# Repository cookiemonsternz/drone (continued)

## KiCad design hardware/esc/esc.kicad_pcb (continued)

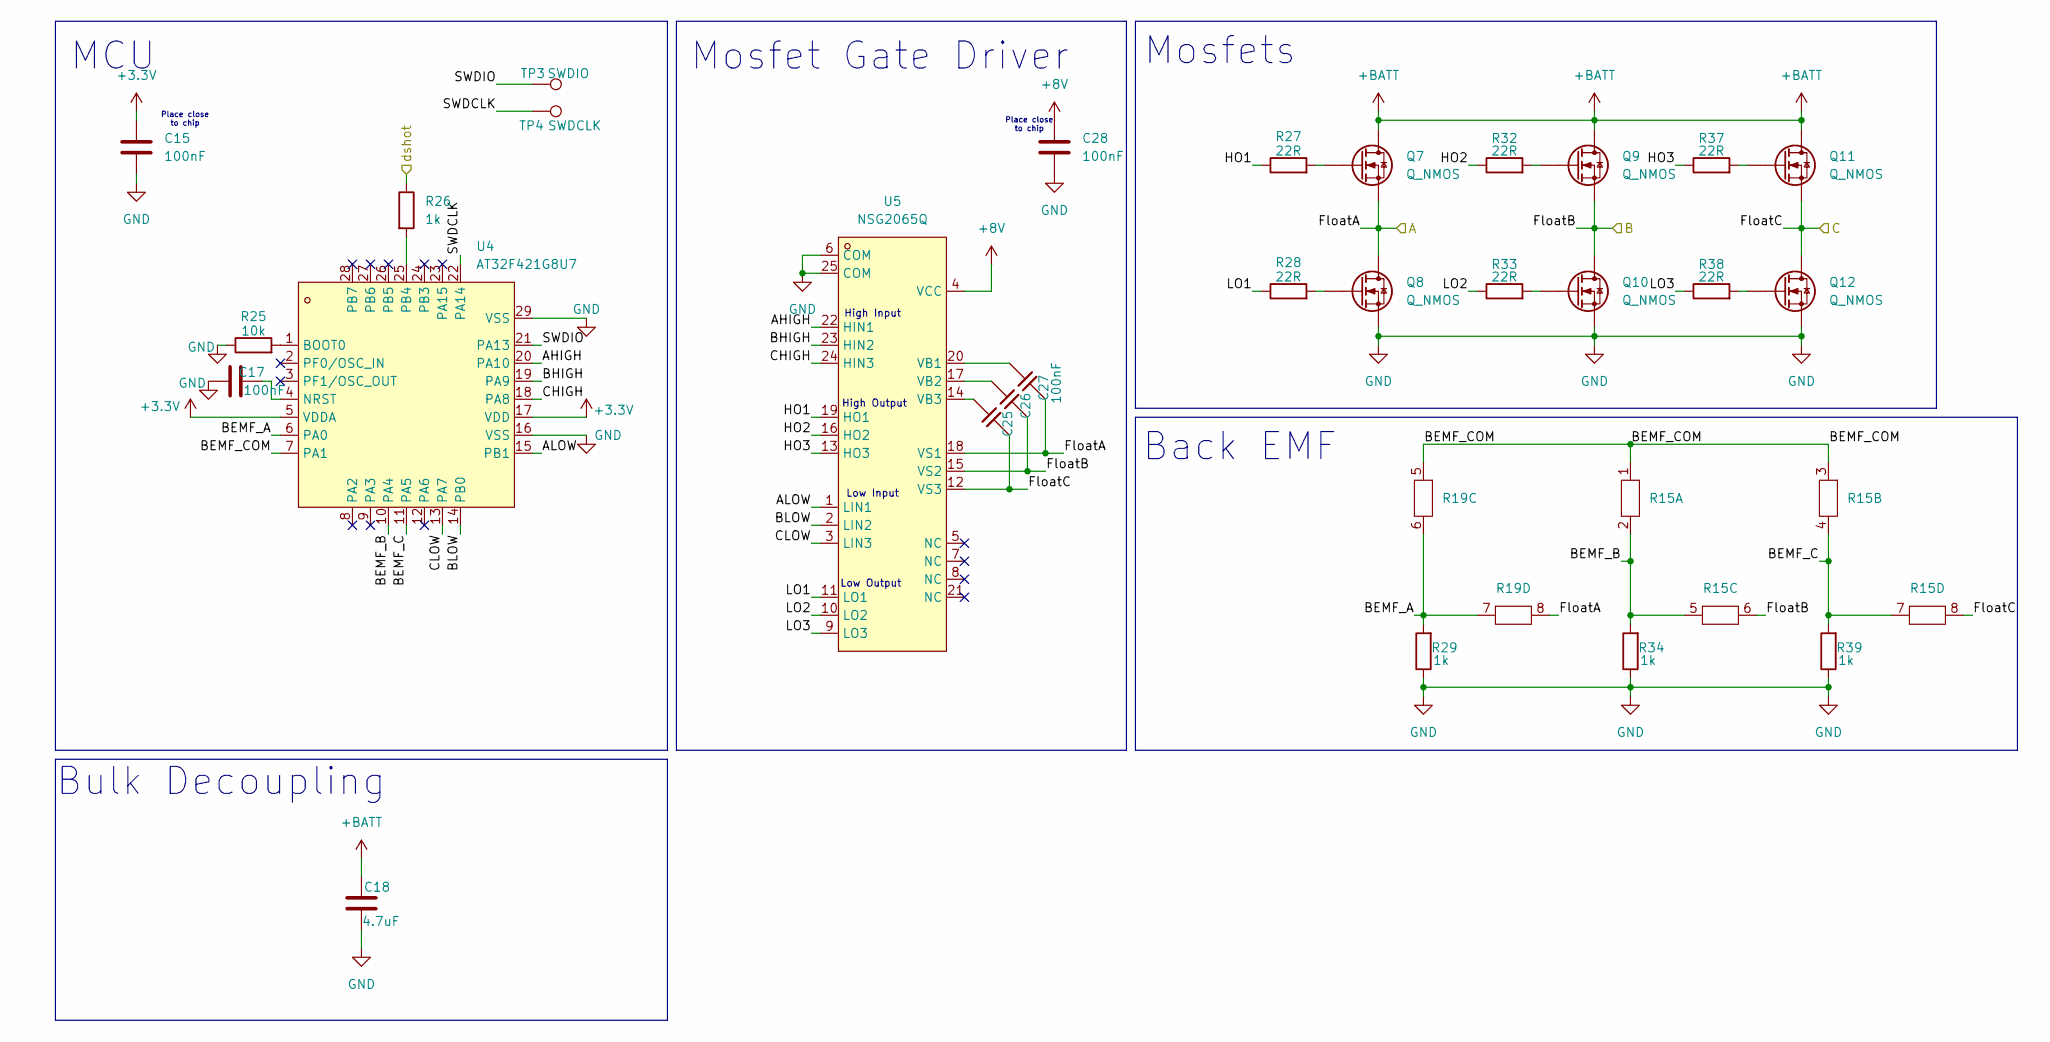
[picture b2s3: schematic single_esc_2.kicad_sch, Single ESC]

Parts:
C15, C17, C25, C26, C27, C28: 100nF; C_0402_1005Metric
C18: 4.7uF; C_0603_1608Metric
Q7, Q8, Q9, Q10, Q11, Q12: Q_NMOS; POWERPAK-1212-8_L3.0-W3.0-P0.65-LS3.3-BL
R15, R19: RES_4D03_0603_3P2X1P6_ROH
R25: 10k; R_0402_1005Metric
R26, R29, R34, R39: 1k; R_0402_1005Metric
R27, R28, R32, R33, R37, R38: 22R; R_0402_1005Metric
TP3: SWDIO; TestPoint_Pad_D1.0mm
TP4: SWDCLK; TestPoint_Pad_D1.0mm
U4: AT32F421G8U7; QFN-28_L4.0-W4.0-P0.40-TL-EP2.4; LCSC Part C2765098
U5: NSG2065Q; QFN-24_L4.0-W4.0-P0.50-TL-EP2.8; LCSC Part C41414478

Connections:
+3.3V: C15.1, U4.5 (VDDA), U4.17 (VDD); also elsewhere on the board
+8V: C28.1, U5.4 (VCC); also elsewhere on the board
+BATT: C18.1, Q7.D, Q9.D, Q11.D; also elsewhere on the board
/ESC2/AHIGH: U4.20 (PA10), U5.22 (HIN1)
/ESC2/ALOW: U4.15 (PB1), U5.1 (LIN1)
/ESC2/BEMF_A: R19.6, R19.7, R29.2, U4.6 (PA0)
/ESC2/BEMF_B: R15.2, R15.5, R34.2, U4.10 (PA4)
/ESC2/BEMF_C: R15.4, R15.7, R39.2, U4.11 (PA5)
/ESC2/BEMF_COM: R15.1, R15.3, R19.5, U4.7 (PA1)
/ESC2/BHIGH: U4.19 (PA9), U5.23 (HIN2)
/ESC2/BLOW: U4.14 (PB0), U5.2 (LIN2)
/ESC2/CHIGH: U4.18 (PA8), U5.24 (HIN3)
/ESC2/CLOW: U4.13 (PA7), U5.3 (LIN3)
/ESC2/FloatA: C27.1, Q7.S, Q8.D, R19.8, U5.18 (VS1); also elsewhere on the board
/ESC2/FloatB: C26.1, Q9.S, Q10.D, R15.6, U5.15 (VS2); also elsewhere on the board
/ESC2/FloatC: C25.1, Q11.S, Q12.D, R15.8, U5.12 (VS3); also elsewhere on the board
/ESC2/HO1: R27.1, U5.19 (HO1)
/ESC2/HO2: R32.1, U5.16 (HO2)
/ESC2/HO3: R37.1, U5.13 (HO3)
/ESC2/LO1: R28.1, U5.11 (LO1)
/ESC2/LO2: R33.1, U5.10 (LO2)
/ESC2/LO3: R38.1, U5.9 (LO3)
/ESC2/SWDCLK: TP4.1, U4.22 (PA14); also elsewhere on the board
/ESC2/SWDIO: TP3.1, U4.21 (PA13); also elsewhere on the board
/dshot_2: R26.1; also elsewhere on the board
GND: C15.2, C17.2, C18.2, C28.2, Q8.S, Q10.S, Q12.S, R25.1, R29.1, R34.1, R39.1, U4.16 (VSS), U4.29 (VSS), U5.6 (COM), U5.25 (COM); also elsewhere on the board
unnamed: Q7.G, R27.2
unnamed: Q8.G, R28.2
unnamed: Q9.G, R32.2
unnamed: Q10.G, R33.2
unnamed: Q11.G, R37.2
unnamed: Q12.G, R38.2
unnamed: R25.2, U4.1 (BOOT0)
unnamed: C17.1, U4.4 (NRST)
unnamed: R26.2, U4.25 (PB4)
unnamed: C27.2, U5.20 (VB1)
unnamed: C26.2, U5.17 (VB2)
unnamed: C25.2, U5.14 (VB3)

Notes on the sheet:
MCU
High Output
Back EMF
High Input
Mosfet Gate Driver
Mosfets
Bulk Decoupling
Low Output
Place close to chip
Low Input

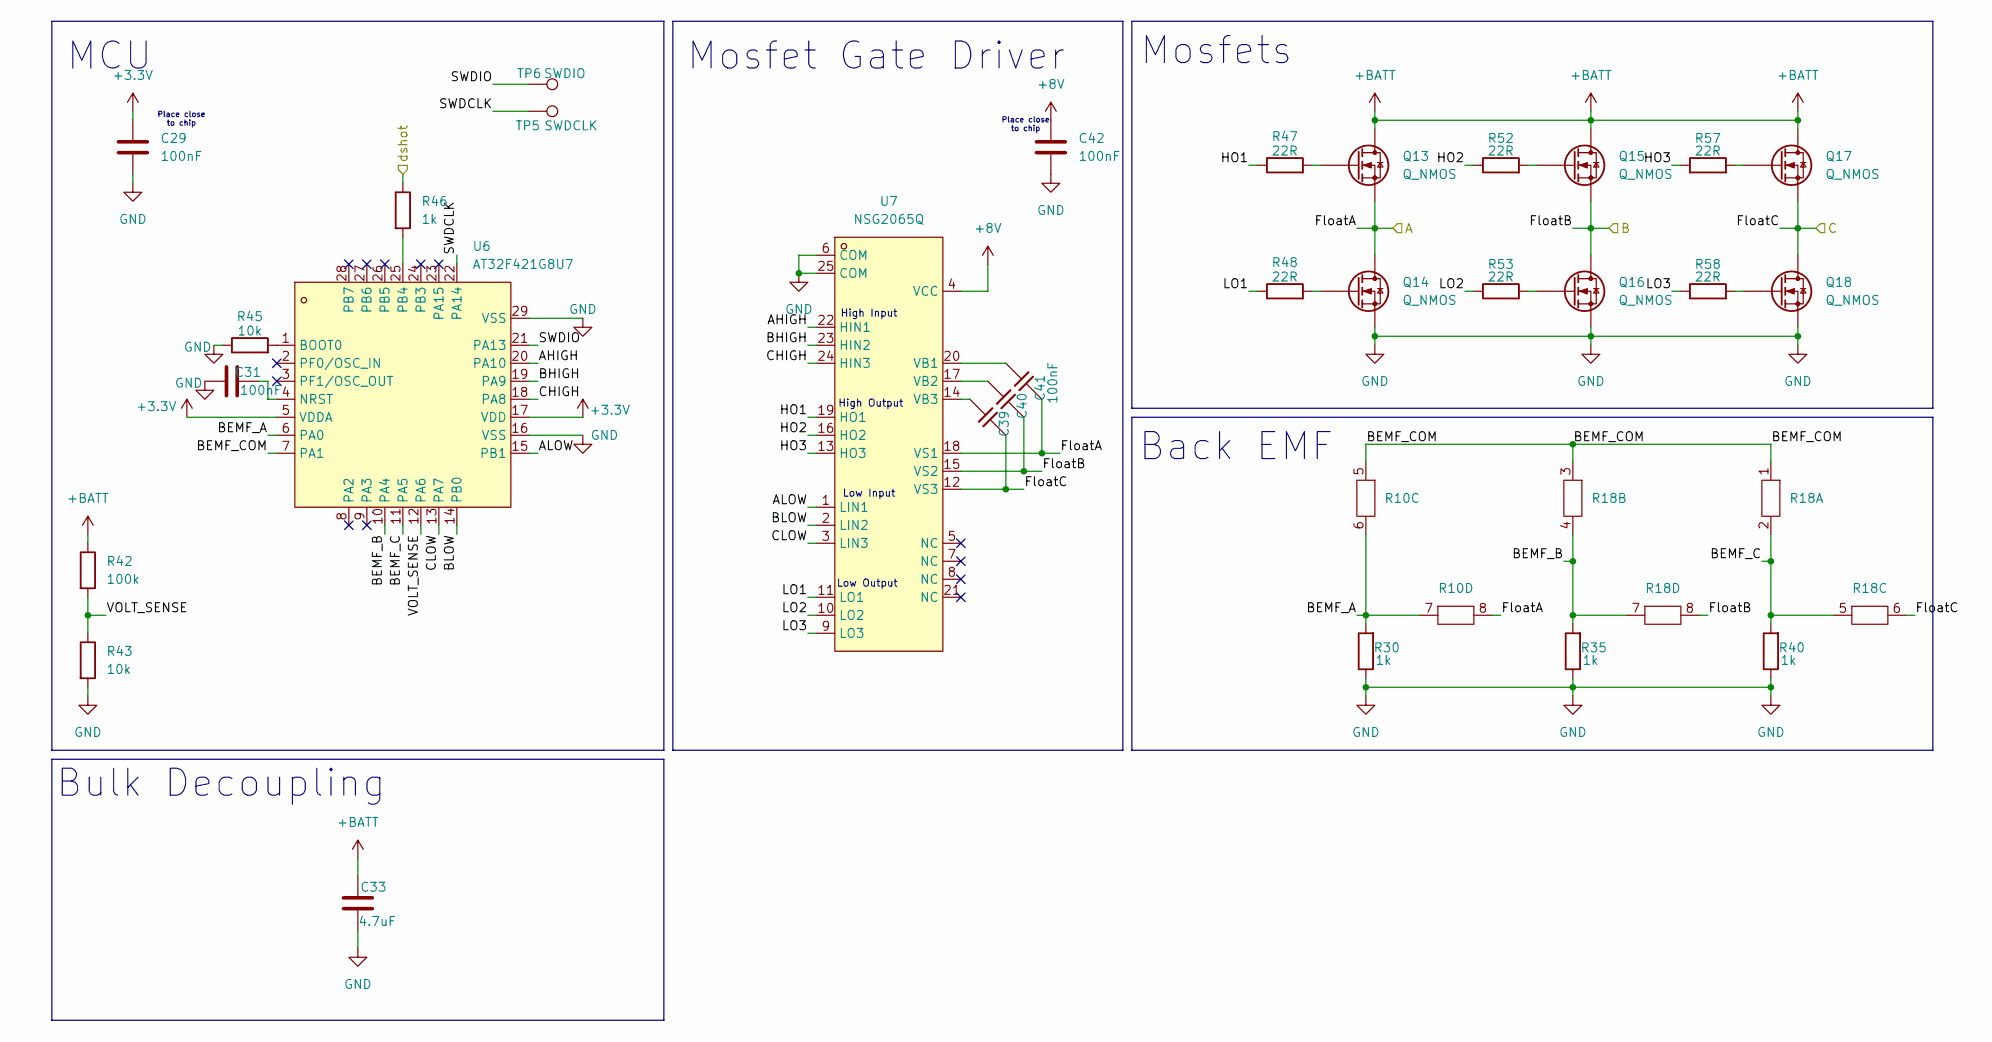
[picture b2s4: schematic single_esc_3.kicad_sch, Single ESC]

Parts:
C29, C31, C39, C40, C41, C42: 100nF; C_0402_1005Metric
C33: 4.7uF; C_0603_1608Metric
Q13, Q14, Q15, Q16, Q17, Q18: Q_NMOS; POWERPAK-1212-8_L3.0-W3.0-P0.65-LS3.3-BL
R10, R18: RES_4D03_0603_3P2X1P6_ROH
R30, R35, R40, R46: 1k; R_0402_1005Metric
R42: 100k; R_0402_1005Metric
R43, R45: 10k; R_0402_1005Metric
R47, R48, R52, R53, R57, R58: 22R; R_0402_1005Metric
TP5: SWDCLK; TestPoint_Pad_D1.0mm
TP6: SWDIO; TestPoint_Pad_D1.0mm
U6: AT32F421G8U7; QFN-28_L4.0-W4.0-P0.40-TL-EP2.4; LCSC Part C2765098
U7: NSG2065Q; QFN-24_L4.0-W4.0-P0.50-TL-EP2.8; LCSC Part C41414478

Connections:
+3.3V: C29.1, U6.5 (VDDA), U6.17 (VDD); also elsewhere on the board
+8V: C42.1, U7.4 (VCC); also elsewhere on the board
+BATT: C33.1, Q13.D, Q15.D, Q17.D, R42.1; also elsewhere on the board
/ESC3/AHIGH: U6.20 (PA10), U7.22 (HIN1)
/ESC3/ALOW: U6.15 (PB1), U7.1 (LIN1)
/ESC3/BEMF_A: R10.6, R10.7, R30.2, U6.6 (PA0)
/ESC3/BEMF_B: R18.4, R18.7, R35.2, U6.10 (PA4)
/ESC3/BEMF_C: R18.2, R18.5, R40.2, U6.11 (PA5)
/ESC3/BEMF_COM: R10.5, R18.1, R18.3, U6.7 (PA1)
/ESC3/BHIGH: U6.19 (PA9), U7.23 (HIN2)
/ESC3/BLOW: U6.14 (PB0), U7.2 (LIN2)
/ESC3/CHIGH: U6.18 (PA8), U7.24 (HIN3)
/ESC3/CLOW: U6.13 (PA7), U7.3 (LIN3)
/ESC3/FloatA: C41.1, Q13.S, Q14.D, R10.8, U7.18 (VS1); also elsewhere on the board
/ESC3/FloatB: C40.1, Q15.S, Q16.D, R18.8, U7.15 (VS2); also elsewhere on the board
/ESC3/FloatC: C39.1, Q17.S, Q18.D, R18.6, U7.12 (VS3); also elsewhere on the board
/ESC3/HO1: R47.1, U7.19 (HO1)
/ESC3/HO2: R52.1, U7.16 (HO2)
/ESC3/HO3: R57.1, U7.13 (HO3)
/ESC3/LO1: R48.1, U7.11 (LO1)
/ESC3/LO2: R53.1, U7.10 (LO2)
/ESC3/LO3: R58.1, U7.9 (LO3)
/ESC3/SWDCLK: TP5.1, U6.22 (PA14); also elsewhere on the board
/ESC3/SWDIO: TP6.1, U6.21 (PA13); also elsewhere on the board
/ESC3/VOLT_SENSE: R42.2, R43.1, U6.12 (PA6)
/dshot_3: R46.1; also elsewhere on the board
GND: C29.2, C31.2, C33.2, C42.2, Q14.S, Q16.S, Q18.S, R30.1, R35.1, R40.1, R43.2, R45.1, U6.16 (VSS), U6.29 (VSS), U7.6 (COM), U7.25 (COM); also elsewhere on the board
unnamed: Q13.G, R47.2
unnamed: Q14.G, R48.2
unnamed: Q15.G, R52.2
unnamed: Q16.G, R53.2
unnamed: Q17.G, R57.2
unnamed: Q18.G, R58.2
unnamed: R45.2, U6.1 (BOOT0)
unnamed: C31.1, U6.4 (NRST)
unnamed: R46.2, U6.25 (PB4)
unnamed: C41.2, U7.20 (VB1)
unnamed: C40.2, U7.17 (VB2)
unnamed: C39.2, U7.14 (VB3)

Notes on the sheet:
Low Output
Low Input
Mosfet Gate Driver
Place close to chip
MCU
Bulk Decoupling
Back EMF
Mosfets
High Input
High Output

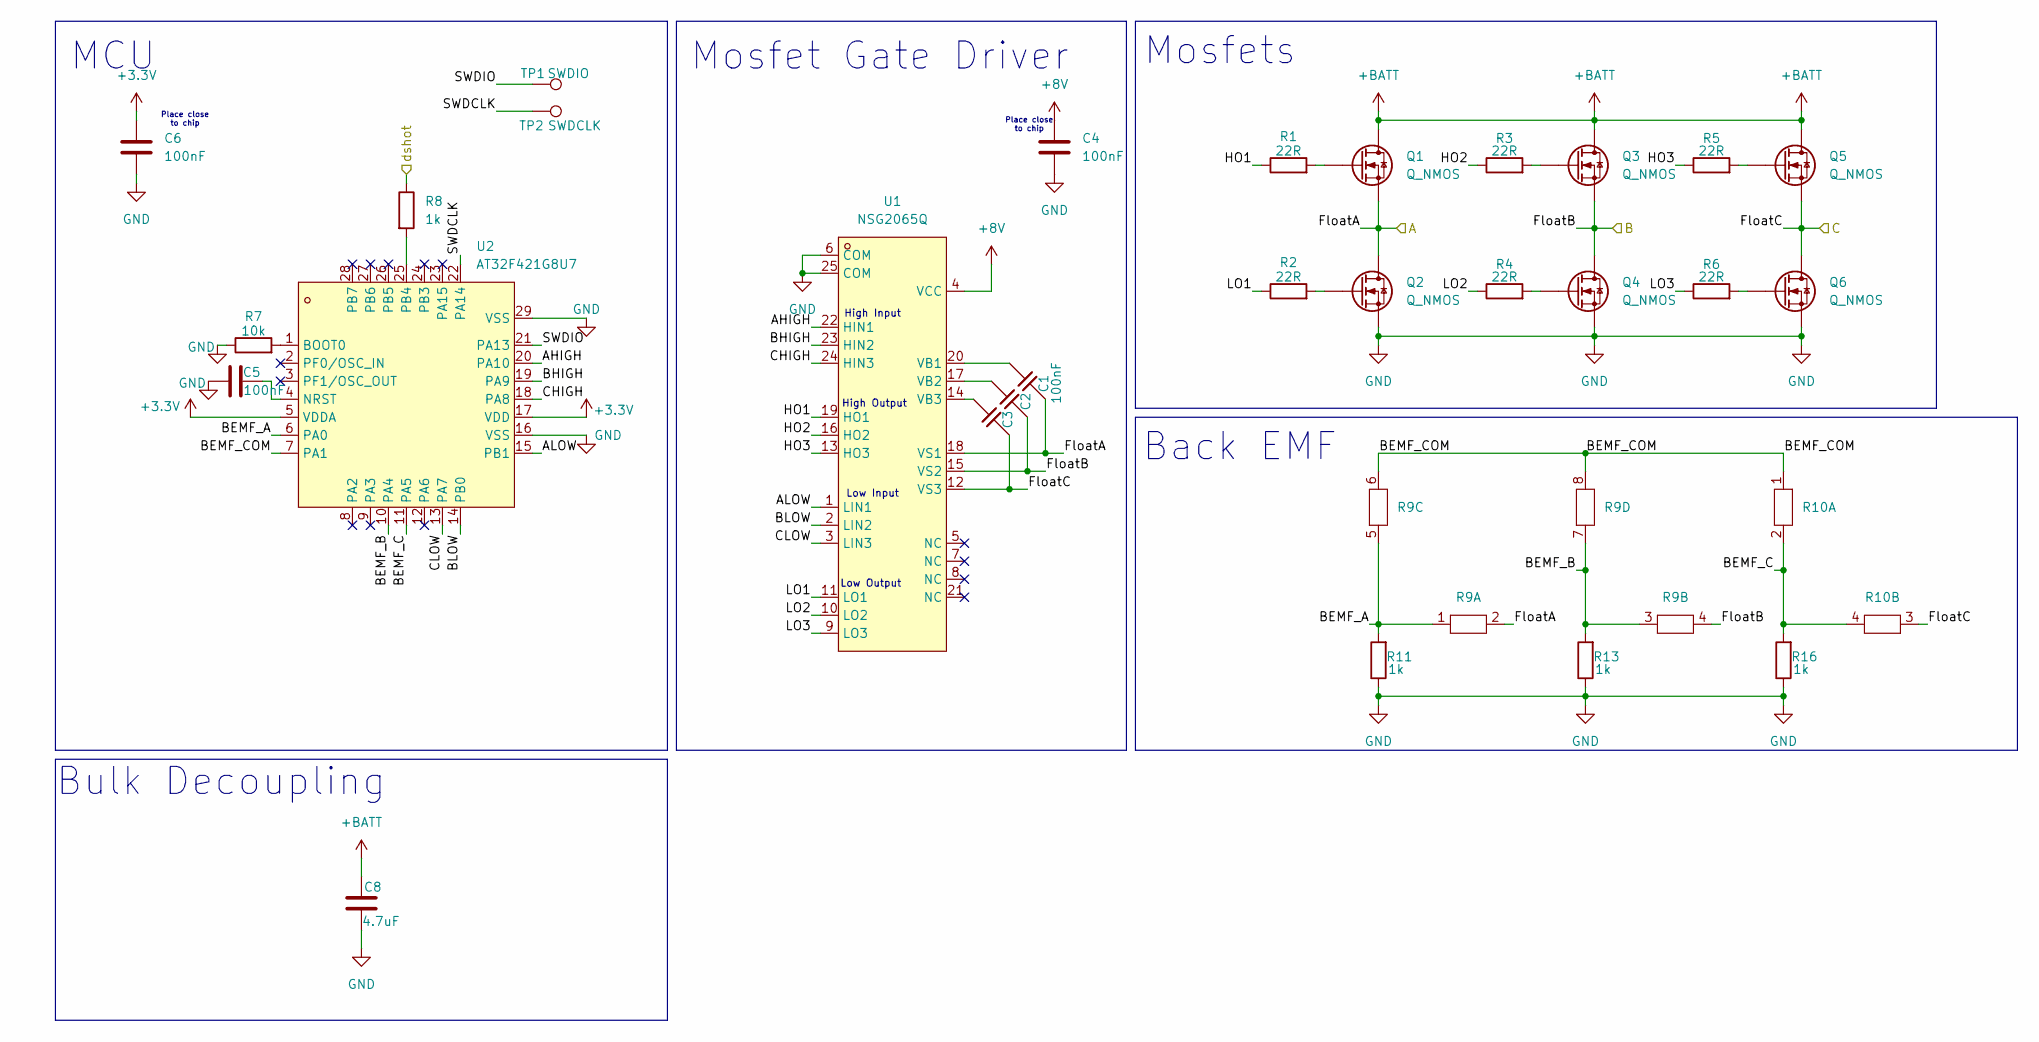
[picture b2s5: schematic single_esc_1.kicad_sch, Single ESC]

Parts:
C1, C2, C3, C4, C5, C6: 100nF; C_0402_1005Metric
C8: 4.7uF; C_0603_1608Metric
Q1, Q2, Q3, Q4, Q5, Q6: Q_NMOS; POWERPAK-1212-8_L3.0-W3.0-P0.65-LS3.3-BL
R1, R2, R3, R4, R5, R6: 22R; R_0402_1005Metric
R7: 10k; R_0402_1005Metric
R8, R11, R13, R16: 1k; R_0402_1005Metric
R9, R10: RES_4D03_0603_3P2X1P6_ROH
TP1: SWDIO; TestPoint_Pad_D1.0mm
TP2: SWDCLK; TestPoint_Pad_D1.0mm
U1: NSG2065Q; QFN-24_L4.0-W4.0-P0.50-TL-EP2.8; LCSC Part C41414478
U2: AT32F421G8U7; QFN-28_L4.0-W4.0-P0.40-TL-EP2.4; LCSC Part C2765098

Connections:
+3.3V: C6.1, U2.5 (VDDA), U2.17 (VDD); also elsewhere on the board
+8V: C4.1, U1.4 (VCC); also elsewhere on the board
+BATT: C8.1, Q1.D, Q3.D, Q5.D; also elsewhere on the board
/ESC1/AHIGH: U1.22 (HIN1), U2.20 (PA10)
/ESC1/ALOW: U1.1 (LIN1), U2.15 (PB1)
/ESC1/BEMF_A: R9.1, R9.5, R11.2, U2.6 (PA0)
/ESC1/BEMF_B: R9.3, R9.7, R13.2, U2.10 (PA4)
/ESC1/BEMF_C: R10.2, R10.4, R16.2, U2.11 (PA5)
/ESC1/BEMF_COM: R9.6, R9.8, R10.1, U2.7 (PA1)
/ESC1/BHIGH: U1.23 (HIN2), U2.19 (PA9)
/ESC1/BLOW: U1.2 (LIN2), U2.14 (PB0)
/ESC1/CHIGH: U1.24 (HIN3), U2.18 (PA8)
/ESC1/CLOW: U1.3 (LIN3), U2.13 (PA7)
/ESC1/FloatA: C1.1, Q1.S, Q2.D, R9.2, U1.18 (VS1); also elsewhere on the board
/ESC1/FloatB: C2.1, Q3.S, Q4.D, R9.4, U1.15 (VS2); also elsewhere on the board
/ESC1/FloatC: C3.1, Q5.S, Q6.D, R10.3, U1.12 (VS3); also elsewhere on the board
/ESC1/HO1: R1.1, U1.19 (HO1)
/ESC1/HO2: R3.1, U1.16 (HO2)
/ESC1/HO3: R5.1, U1.13 (HO3)
/ESC1/LO1: R2.1, U1.11 (LO1)
/ESC1/LO2: R4.1, U1.10 (LO2)
/ESC1/LO3: R6.1, U1.9 (LO3)
/ESC1/SWDCLK: TP2.1, U2.22 (PA14); also elsewhere on the board
/ESC1/SWDIO: TP1.1, U2.21 (PA13); also elsewhere on the board
/dshot_1: R8.1; also elsewhere on the board
GND: C4.2, C5.2, C6.2, C8.2, Q2.S, Q4.S, Q6.S, R7.1, R11.1, R13.1, R16.1, U1.6 (COM), U1.25 (COM), U2.16 (VSS), U2.29 (VSS); also elsewhere on the board
unnamed: Q1.G, R1.2
unnamed: Q2.G, R2.2
unnamed: Q3.G, R3.2
unnamed: Q4.G, R4.2
unnamed: Q5.G, R5.2
unnamed: Q6.G, R6.2
unnamed: C1.2, U1.20 (VB1)
unnamed: C2.2, U1.17 (VB2)
unnamed: C3.2, U1.14 (VB3)
unnamed: R7.2, U2.1 (BOOT0)
unnamed: C5.1, U2.4 (NRST)
unnamed: R8.2, U2.25 (PB4)

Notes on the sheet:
High Output
Mosfet Gate Driver
High Input
MCU
Place close to chip
Low Output
Mosfets
Low Input
Back EMF
Bulk Decoupling

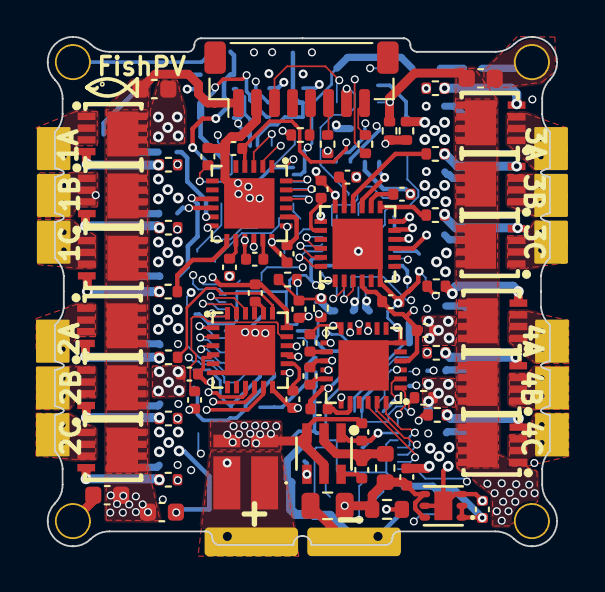
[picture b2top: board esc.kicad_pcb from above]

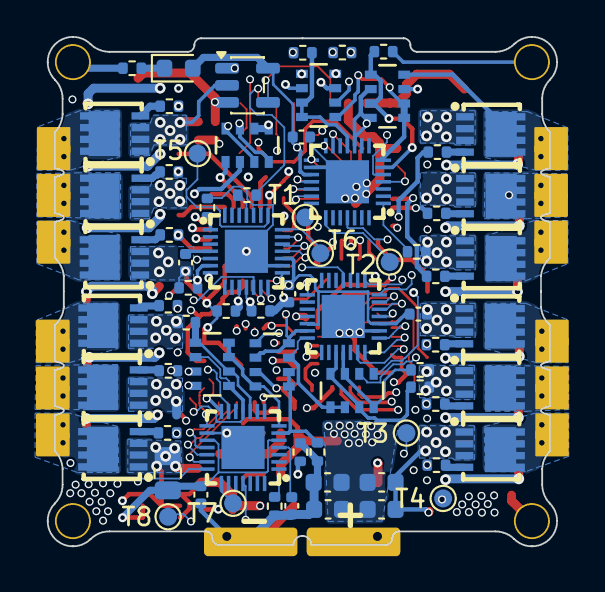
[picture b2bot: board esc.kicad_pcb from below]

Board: 6 copper layers, 28.3 x 28.3 mm, 141 parts (71 on the bottom side), 147 nets.

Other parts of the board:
T1, T3, T6, T8: SWDIO; TestPoint_Pad_D1.0mm
T2, T4, T5, T7: SWDCLK; TestPoint_Pad_D1.0mm

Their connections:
/ESC1/SWDCLK: T2.1 (1_1); also elsewhere on the board
/ESC1/SWDIO: T1.1 (1_1); also elsewhere on the board
/ESC2/SWDCLK: T4.1 (1_1); also elsewhere on the board
/ESC2/SWDIO: T3.1 (1_1); also elsewhere on the board
/ESC3/SWDCLK: T5.1 (1_1); also elsewhere on the board
/ESC3/SWDIO: T6.1 (1_1); also elsewhere on the board
/ESC4/SWDCLK: T7.1 (1_1); also elsewhere on the board
/ESC4/SWDIO: T8.1 (1_1); also elsewhere on the board

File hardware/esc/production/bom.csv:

Designator,Footprint,Quantity,Value,LCSC Part #
"C1, C15, C17, C2, C25, C26, C27, C28, C29, C3, C31, C39, C4, C40, C41, C42, C43, C45, C5, C53, C54, C55, C56, C57, C58, C6, C61, C62",0402,28,100nF,
"C10, C11, C7, C9",0603,4,22uF,
"C18, C33, C46, C8",0603,4,4.7uF,
"C59, C63",0805,2,22uF,
D4,0603,1,LED,
J1,JST_SH_BM08B-SRSS-TB_1x08-1MP_P1.00mm_Vertical,1,JST SH 1.0mm,
L1,0603,1,XRIM160808SR47MBCD,
"Q1, Q10, Q11, Q12, Q13, Q14, Q15, Q16, Q17, Q18, Q19, Q2, Q20, Q21, Q22, Q23, Q24, Q3, Q4, Q5, Q6, Q7, Q8, Q9",POWERPAK-1212-8_L3.0-W3.0-P0.65-LS3.3-BL,24,Q_NMOS,
"R1, R2, R27, R28, R3, R32, R33, R37, R38, R4, R47, R48, R5, R52, R53, R57, R58, R6, R67, R68, R72, R73, R77, R78",0402,24,22R,
"R10, R15, R18, R19, R22, R9",RES_4D03_0603_3P2X1P6_ROH,6,~,
"R11, R13, R16, R26, R29, R30, R31, R34, R35, R36, R39, R40, R46, R49, R66, R8",0402,16,1k,
R21,BVNZR000510,1,0.5m,
"R25, R43, R45, R65, R7, R83",0402,6,10k,
R42,0402,1,100k,
R64,0402,1,2.2k,
R82,0603,1,124k,
"T1, T3, T6, T8",TestPoint_Pad_D1.0mm,4,SWDIO,
"T2, T4, T5, T7",TestPoint_Pad_D1.0mm,4,SWDCLK,
"U1, U5, U7, U9",QFN-24_L4.0-W4.0-P0.50-TL-EP2.8,4,NSG2065Q,C41414478
U10,WSON-6_L2.0-W2.0-P0.65-TL-EP,1,TLV76733DRVR,C2848334
U11,SOT-23-6_L2.9-W1.6-P0.95-LS2.9-BL,1,LMR51420YDDCR,C5383002
"U2, U4, U6, U8",QFN-28_L4.0-W4.0-P0.40-TL-EP2.4,4,AT32F421G8U7,C2765098
U3,SOT-23-5,1,INA180B2,

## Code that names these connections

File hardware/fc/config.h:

/*
 * This file is part of Betaflight.
 *
 * Betaflight is free software. You can redistribute this software
 * and/or modify this software under the terms of the GNU General
 * Public License as published by the Free Software Foundation,
 * either version 3 of the License, or (at your option) any later
 * version.
 *
 * Betaflight is distributed in the hope that it will be useful,
 * but WITHOUT ANY WARRANTY; without even the implied warranty of
 * MERCHANTABILITY or FITNESS FOR A PARTICULAR PURPOSE.
 *
 * See the GNU General Public License for more details.
 *
 * You should have received a copy of the GNU General Public
 * License along with this software.
 *
 * If not, see <http://www.gnu.org/licenses/>.
 */

#pragma once

#define FC_TARGET_MCU     STM32F405

/* TODO RENAME BOARD */
#define BOARD_NAME        MYDRONEIDK
#define MANUFACTURER_ID   CUST

#define USE_ACC
#define USE_GYRO

#define USE_ACC_SPI_ICM42688P
#define USE_GYRO_SPI_ICM42688P

#define USE_BARO
#define USE_BARO_BMP280

#define USE_FLASH
#define USE_FLASH_M25P16

#define USE_MAX7456

// I/O
#define LED0_PIN             PC15
#define LED1_PIN             PC14
#define BEEPER_PIN           PC13
#define BEEPER_INVERTED

// ACC/GYRO SPI 1
#define USE_SPI_GYRO
#define GYRO_1_EXTI_PIN      PC4
#define GYRO_1_CS_PIN        PA4
#define GYRO_1_SPI_INSTANCE  SPI1
#define GYRO_1_CLKIN_PIN     PB8
#define GYRO_1_ALIGN         CW0_DEG

#define SPI1_SCK_PIN         PA5
#define SPI1_SDI_PIN         PA6
#define SPI1_SDO_PIN         PA7

// FLASH SPI 2
#define SPI2_SCK_PIN         PB13
#define SPI2_SDI_PIN         PB14
#define SPI2_SDO_PIN         PB15

#define FLASH_CS_PIN         PB12
#define FLASH_SPI_INSTANCE   SPI2

// OSD SPI 3
#define SPI3_SCK_PIN         PC10
#define SPI3_SDI_PIN         PC11
#define SPI3_SDO_PIN         PB5

#define MAX7456_SPI_CS_PIN   PA15
#define MAX7456_SPI_INSTANCE SPI3

// ADC
#define USE_ADC
#define ADC_VBAT_PIN         PC1
// #define ADC_RSSI_PIN         PC2
#define ADC_CURR_PIN         PC2
#define ADC_INSTANCE         ADC1

// UART PORTS
// UART1 - ELRS
#define UART1_TX_PIN         PB6
#define UART1_RX_PIN         PB7

// UART2 
// #define UART2_TX_PIN         PA2
// #define UART2_RX_PIN         PA3

// UART2 
// #define UART3_TX_PIN         PB10
// #define UART3_RX_PIN         PB11

// UART3 
// #define UART4_TX_PIN         PA0
// #define UART4_RX_PIN         PA1

// UART4 
// #define UART5_TX_PIN         PC12
// #define UART5_RX_PIN         PD2

// UART5
// #define UART6_TX_PIN         PC6
// #define UART6_RX_PIN         PC7

// TIMERS
#define TIMER_PIN_MAPPING \
    TIMER_PIN_MAP( 0, PA9 , 1,  1) \
    TIMER_PIN_MAP( 1, PA8 , 1,  1) \
    TIMER_PIN_MAP( 2, PC9 , 1,  0) \
    TIMER_PIN_MAP( 3, PC8 , 1,  0) \
    TIMER_PIN_MAP( 4, PB3 , 1,  0)

// MOTORS PINOUT
#define MOTOR1_PIN           PA9
#define MOTOR2_PIN           PA8
#define MOTOR3_PIN           PC9
#define MOTOR4_PIN           PC8

#define ADC1_DMA_OPT         1

// BARO I2C
#define BARO_I2C_INSTANCE I2CDEV_2
#define MAG_I2C_INSTANCE I2CDEV_2

#define I2C1_SCL_PIN         PB10
#define I2C1_SDA_PIN         PB11

// USERS
#define PINIO1_PIN           PB1
#define PINIO1_BOX 40
#define PINIO1_CONFIG 129

// DEFAULTS
#define DEFAULT_BLACKBOX_DEVICE         BLACKBOX_DEVICE_FLASH
#define DEFAULT_CURRENT_METER_SOURCE    CURRENT_METER_ADC
#define DEFAULT_VOLTAGE_METER_SOURCE    VOLTAGE_METER_ADC
#define DEFAULT_VOLTAGE_METER_SCALE     102
#define DEFAULT_DSHOT_BURST             DSHOT_DMAR_OFF
#define DEFAULT_DSHOT_BITBANG           DSHOT_BITBANG_OFF
#define SYSTEM_HSE_MHZ                  8

// DISABLED
// #define INVERTER_PIN_UART1   PC0
// #define ESCSERIAL_PIN        PB9

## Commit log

2026-03-25 inti
2026-03-30 stuffs
2026-03-30 gitignore
2026-04-02 ESC Layout try 1
2026-04-02 journal for 2nd april
2026-04-03 redo layout and new board outline
2026-04-05 board pcb + res arrays
2026-04-05 Sync for windows
2026-04-07 Routing done!
2026-04-11 start flight controller
2026-04-13 More work on FC
2026-05-21 Finished boards, restructured, readme, sim, and more!
    Former-commit-id: 1faa8c61b1a9c7058c908202a6c3d018e8ff8ca2
2026-05-21 lfs
    Former-commit-id: d8ebaec57af61f51661c7e7436063da323a8d36b
2026-05-30 Add wiring diagram, zine, more readme, bom
    Former-commit-id: 3e30fac0ecf017dfad40331f47e922149ad91b9f
2026-05-30 try to fix lfs
2026-05-30 update bom totals
2026-05-30 Finishing off!
2026-06-25 fix readme
2026-06-26 add . to fix for personal site regex lol
